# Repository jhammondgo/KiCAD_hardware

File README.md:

# KiCAD_hardware
to allow components from GitHub to computer

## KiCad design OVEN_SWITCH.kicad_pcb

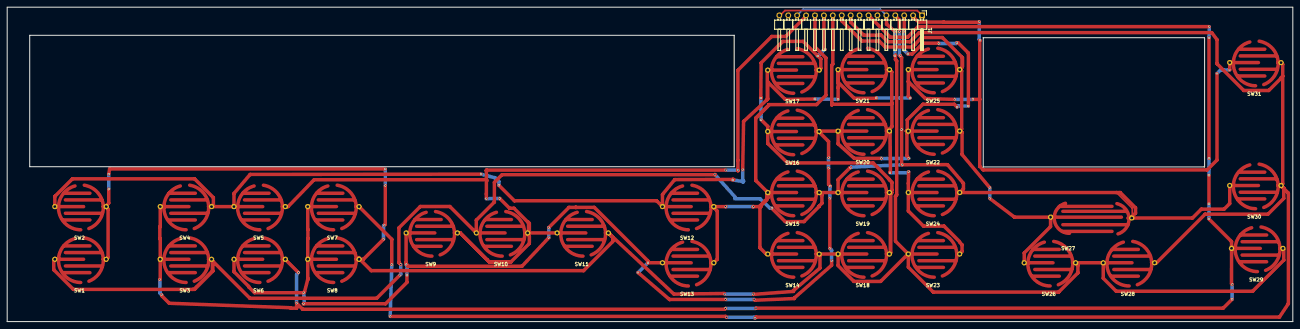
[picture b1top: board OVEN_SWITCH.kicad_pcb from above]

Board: 2 copper layers, 366.0 x 89.5 mm, 32 parts (0 on the bottom side), 12 nets.

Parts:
J1: CONN_01X17; Pin_Header_Angled_1x17_Pitch2.54mm
SW1: LOWER OVEN; Membrane_Switch
SW2: UPPER OVEN; Membrane_Switch
SW3, SW4: BAKE; Membrane_Switch
SW5, SW6: BROIL; Membrane_Switch
SW7: CLEAN; Membrane_Switch
SW8: ROAST; Membrane_Switch
SW9: BAKED GOODS; Membrane_Switch
SW10: MEATS; Membrane_Switch
SW11: OTHER FOODS; Membrane_Switch
SW12: COOK TIME; Membrane_Switch
SW13: STOP TIME; Membrane_Switch
SW14: CONVECT FULL MEAL; Membrane_Switch
SW15: 7; Membrane_Switch
SW16: 4; Membrane_Switch
SW17: 1; Membrane_Switch
SW18: 0; Membrane_Switch
SW19: 8; Membrane_Switch
SW20: 5; Membrane_Switch
SW21: 2; Membrane_Switch
SW22: 6; Membrane_Switch
SW23: OVEN LIGHT; Membrane_Switch
SW24: 9; Membrane_Switch
SW25: 3; Membrane_Switch
SW26: SET.START; Membrane_Switch
SW27: CLOCK; Membrane_Switch_Wide
SW28: CANCEL; Membrane_Switch
SW29: LOWER OVEN CANCEL/OFF; Membrane_Switch
SW30: UPPER OVEN CANCEL/OFF; Membrane_Switch
SW31: START; Membrane_Switch

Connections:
unnamed: J1.1, J1.17
unnamed: J1.2, SW2.1, SW4.2, SW5.1, SW12.1, SW17.1, SW21.1, SW25.1, SW31.1
unnamed: J1.3, SW6.1, SW7.1, SW8.1, SW9.1, SW13.1, SW16.2, SW20.1, SW22.1
unnamed: J1.4, SW1.1, SW3.2, SW10.1, SW15.2, SW19.1, SW24.2, SW27.2, SW30.1
unnamed: J1.7, SW3.1, SW4.1, SW6.2, SW29.1
unnamed: J1.9, SW7.2, SW28.2, SW30.2, SW31.2
unnamed: J1.10, SW22.2, SW25.2, SW26.1, SW27.1
unnamed: J1.11, SW20.2, SW21.2, SW23.2, SW24.1
unnamed: J1.12, SW16.1, SW17.2, SW18.2, SW19.2
unnamed: J1.13, SW12.2, SW13.2, SW14.1, SW15.1
unnamed: J1.14, SW5.2, SW9.2, SW10.2, SW11.1
unnamed: J1.5, J1.15, SW1.2, SW2.2, SW8.2, SW11.2, SW14.2, SW18.1, SW23.1, SW26.2, SW28.1, SW29.2

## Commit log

2017-04-08 Add files via upload
    before moving edge and connector
2017-04-11 After thicker traces and wide clock footprint
2017-04-14 Add files via upload
    files after first CNC prototype of left half
